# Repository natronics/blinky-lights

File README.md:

# blinky-lights

My first 555 project, also an example board for [psu-epl](http://psu-epl.github.com/).

It's a small PCB with a [555 timer](http://en.wikipedia.org/wiki/555_timer_IC)
that drives the clock of a shift register/LED driver IC to make a bunch of
LEDs blink in a turn.

CAD files are made with the a free copy of [EAGLE](http://www.cadsoftusa.com/) version 6.3.0.

## Schematic

## Layout

## BOM

 - 1x 555 Timer
 - 1x Allegro A6278EA LED Driver IC
 - 2x 10 μF Capacitor
 - 1x 0.01 μF Capacitor
 - 2x 1k Ω Resistor
 - 1x 4k Ω Resistor
 - 1x 500 Ω Resistor
 - 1x 10 Ω Resistor
 - 1x N Channel MOSFET (TO-92)
 - 8x 3mm LEDs
 - 1x Spare USB cable

# Build Log

## 2013-04-10

Good working breadboard. Schematic and board layout (should) match what is working on my bench.

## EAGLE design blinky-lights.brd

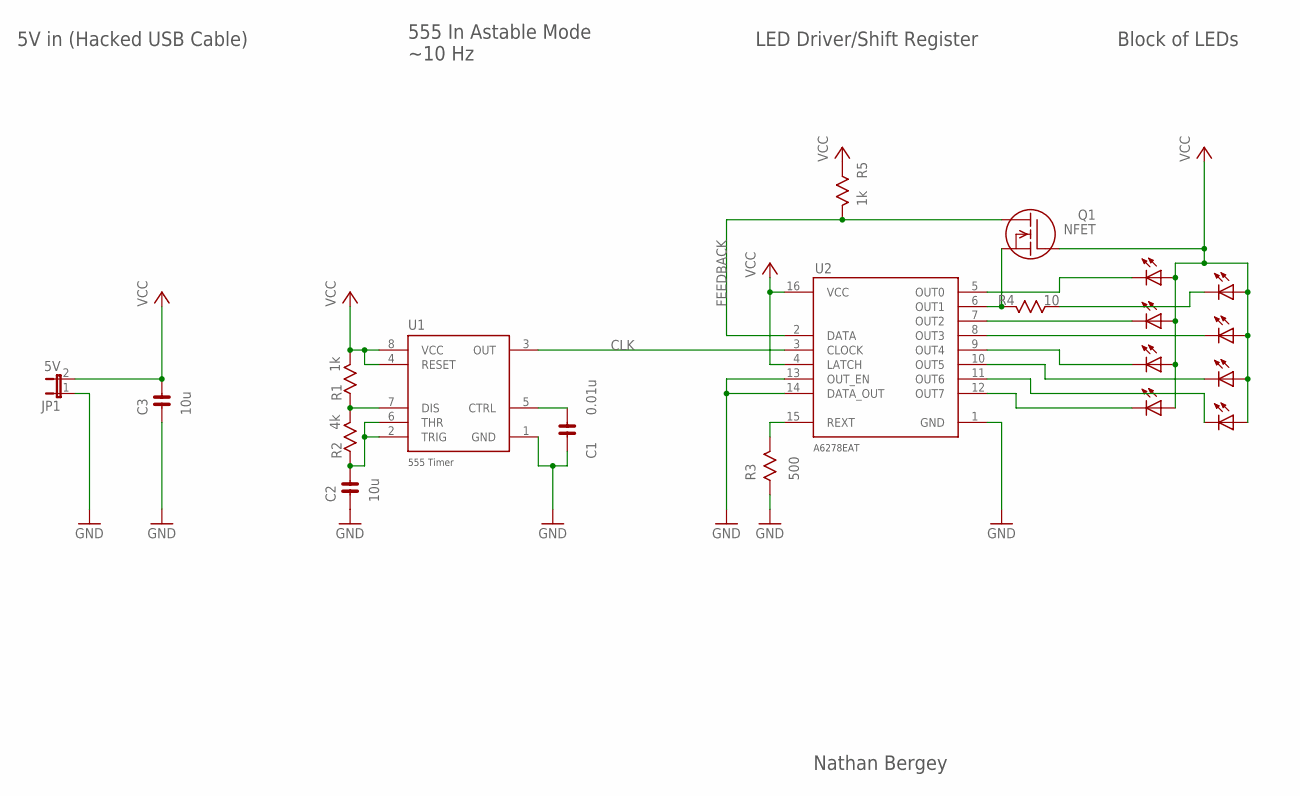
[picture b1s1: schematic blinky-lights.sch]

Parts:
C1: 0.01u; CAP
C2, C3: 10u; CAP
JP1: 5V; JP1
LED0, LED1, LED2, LED3, LED4, LED5, LED6, LED7: LED3MM
Q1: NFET; TO92-EBC
R1, R5: 1k; V234/12
R2: 4k; V234/12
R3: 500; V234/12
R4: 10; V234/12
U1: 555
U2: A2678EAT; A6278EAT

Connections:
CLK: U1.3 (OUT), U2.3 (CLOCK)
FEEDBACK: Q1.D, R5.2 (C), U2.2 (DATA)
GND: C1.C, C2.C, C3.C, JP1.1, R3.1 (A), U1.1 (GND), U2.1 (GND), U2.13 (OUT_EN), U2.14 (DATA_OUT)
unnamed: LED0.K (C), U2.5 (OUT0)
unnamed: LED2.K (C), U2.7 (OUT2)
unnamed: LED4.K (C), U2.9 (OUT4)
unnamed: LED7.K (C), U2.12 (OUT7)
unnamed: Q1.S, R4.2 (C), U2.6 (OUT1)
unnamed: LED3.K (C), U2.8 (OUT3)
unnamed: LED5.K (C), U2.10 (OUT5)
unnamed: LED6.K (C), U2.11 (OUT6)
unnamed: R1.1 (A), R2.2 (C), U1.7 (DIS)
unnamed: C1.A, U1.5 (CTRL)
unnamed: C2.A, R2.1 (A), U1.2 (TRIG), U1.6 (THR)
REXT: R3.2 (C), U2.15 (REXT)
SENSE: LED1.K (C), R4.1 (A)
VCC: C3.A, JP1.2, LED0.A, LED1.A, LED2.A, LED3.A, LED4.A, LED5.A, LED6.A, LED7.A, Q1.G, R1.2 (C), R5.1 (A), U1.4 (RESET), U1.8 (VCC), U2.4 (LATCH), U2.16 (VCC)

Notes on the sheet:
Nathan Bergey
5V in (Hacked USB Cable)
555 In Astable Mode ~10 Hz
LED Driver/Shift Register
Block of LEDs

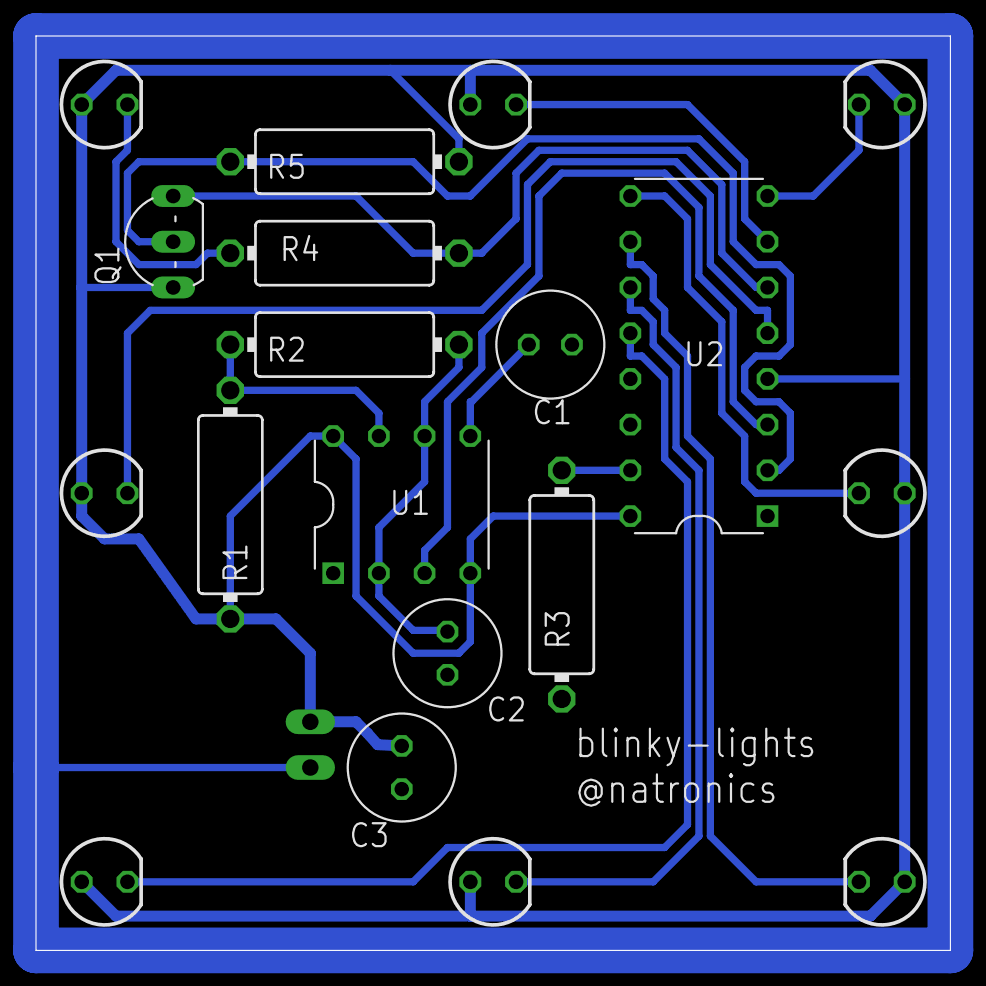
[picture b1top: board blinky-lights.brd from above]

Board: 2 copper layers, 50.8 x 50.8 mm, 20 parts (0 on the bottom side), 17 nets.

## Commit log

2013-03-05 part library with LED driver
2013-03-05 555 Timer in parts library
2013-03-05 simple capacitor part
2013-03-05 fixed capacitor simbol
2013-03-05 schematic
2013-03-05 adding schematic preview
2013-03-05 fixed schematic image uri
2013-03-05 schematic passed ERC
2013-03-06 Feedback with a NPN transistor and pulldown resistor on DATA line. Also added decoupling capacitor at power in
2013-03-06 Capacitor Value
2013-03-06 first pass board layout with not routing
2013-03-10 replaced transistor with a fet
2013-03-10 board layout
2013-03-10 minor cleanup on board
2013-03-10 schematic and board clean up
2013-03-10 board clean up, got rid of last airwire
2013-03-11 board and schematic cleanup
2013-03-11 Finished cleanup and cut a set of gerbers to try and mill
2013-03-11 Added basic BOM
